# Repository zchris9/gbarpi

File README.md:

# gbarpi

# ibom
https://github.com/oceanofthelost/InteractivePCB

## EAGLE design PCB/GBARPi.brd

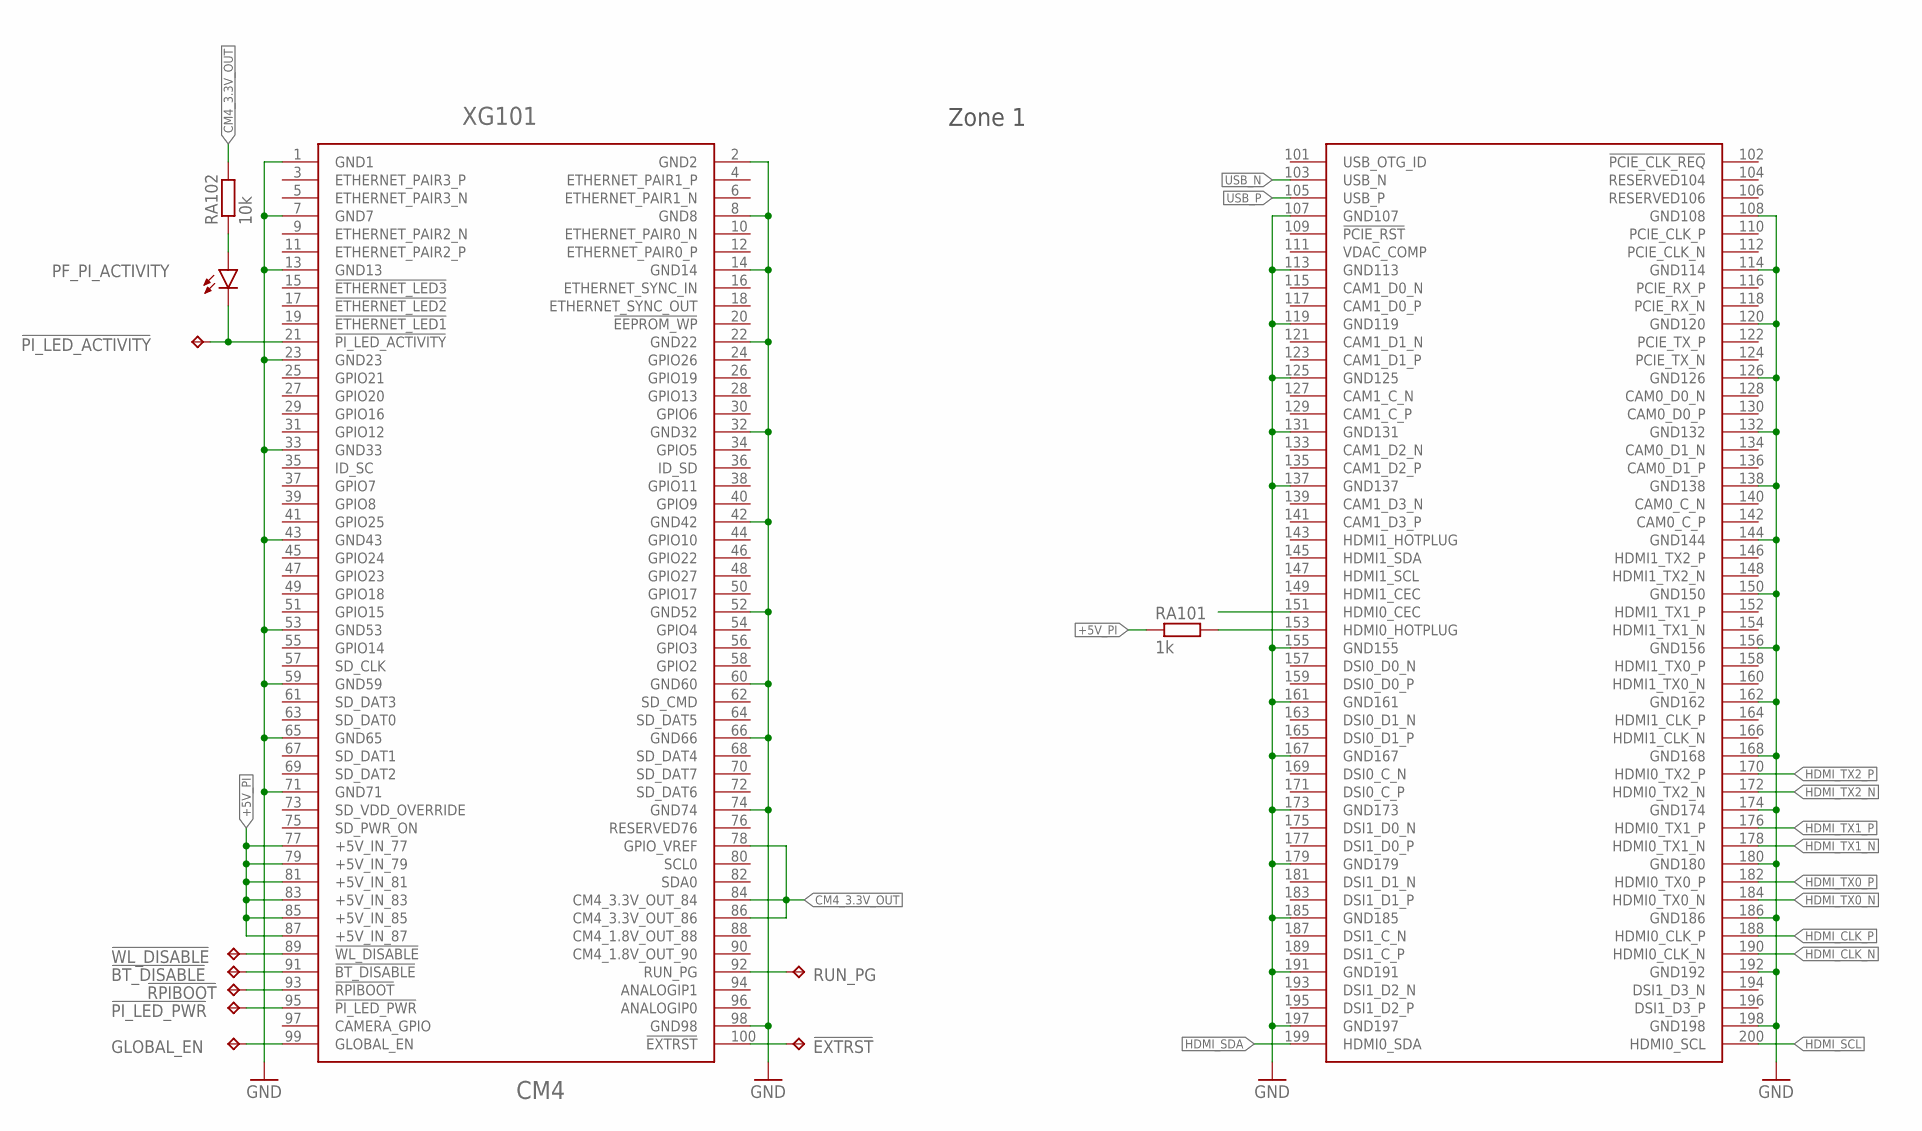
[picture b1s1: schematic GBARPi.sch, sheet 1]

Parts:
!BT_DISABLE: TPB1,27; B1,27
!EXTRST: TPB1,27; B1,27
!PI_LED_ACTIVITY: TPB1,27; B1,27
!PI_LED_PWR: TPB1,27; B1,27
!RPIBOOT: TPB1,27; B1,27
!WL_DISABLE: TPB1,27; B1,27
GLOBAL_EN: TPB1,27; B1,27
PF_PI_ACTIVITY: LEDCHIP-LED0603; CHIP-LED0603
RA101: 1k; R0402
RA102: 10k; R0402
RUN_PG: TPB1,27; B1,27
XG101: CM4

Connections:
!BT_DISABLE: !BT_DISABLE.TP, XG101.91 (!BT_DISABLE)
!EXTRST: !EXTRST.TP, XG101.100 (!EXTRST)
!PI_LED_ACTIVITY: !PI_LED_ACTIVITY.TP, PF_PI_ACTIVITY.C, XG101.21 (!PI_LED_ACTIVITY)
!PI_LED_PWR: !PI_LED_PWR.TP, XG101.95 (!PI_LED_PWR)
!RPIBOOT: !RPIBOOT.TP, XG101.93 (!RPIBOOT)
!WL_DISABLE: !WL_DISABLE.TP, XG101.89 (!WL_DISABLE)
+5V_PI: RA101.1, XG101.77 (+5V_IN_77), XG101.79 (+5V_IN_79), XG101.81 (+5V_IN_81), XG101.83 (+5V_IN_83), XG101.85 (+5V_IN_85), XG101.87 (+5V_IN_87); also elsewhere on the board
CM4_3.3V_OUT: RA102.2, XG101.78 (GPIO_VREF), XG101.84 (CM4_3.3V_OUT_84), XG101.86 (CM4_3.3V_OUT_86)
GLOBAL_EN: GLOBAL_EN.TP, XG101.99 (GLOBAL_EN)
GND: XG101.1 (GND1), XG101.2 (GND2), XG101.7 (GND7), XG101.8 (GND8), XG101.13 (GND13), XG101.14 (GND14), XG101.22 (GND22), XG101.23 (GND23), XG101.32 (GND32), XG101.33 (GND33), XG101.42 (GND42), XG101.43 (GND43), XG101.52 (GND52), XG101.53 (GND53), XG101.59 (GND59), XG101.60 (GND60), XG101.65 (GND65), XG101.66 (GND66), XG101.71 (GND71), XG101.74 (GND74), XG101.98 (GND98), XG101.107 (GND107), XG101.108 (GND108), XG101.113 (GND113), XG101.114 (GND114), XG101.119 (GND119), XG101.120 (GND120), XG101.125 (GND125), XG101.126 (GND126), XG101.131 (GND131), XG101.132 (GND132), XG101.137 (GND137), XG101.138 (GND138), XG101.144 (GND144), XG101.150 (GND150), XG101.155 (GND155), XG101.156 (GND156), XG101.161 (GND161), XG101.162 (GND162), XG101.167 (GND167), XG101.168 (GND168), XG101.173 (GND173), XG101.174 (GND174), XG101.179 (GND179), XG101.180 (GND180), XG101.185 (GND185), XG101.186 (GND186), XG101.191 (GND191), XG101.192 (GND192), XG101.197 (GND197), XG101.198 (GND198); also elsewhere on the board
HDMI_CLK_N: XG101.190 (HDMI0_CLK_N); also elsewhere on the board
HDMI_CLK_P: XG101.188 (HDMI0_CLK_P); also elsewhere on the board
HDMI_SCL: XG101.200 (HDMI0_SCL); also elsewhere on the board
HDMI_SDA: XG101.199 (HDMI0_SDA); also elsewhere on the board
HDMI_TX0_N: XG101.184 (HDMI0_TX0_N); also elsewhere on the board
HDMI_TX0_P: XG101.182 (HDMI0_TX0_P); also elsewhere on the board
HDMI_TX1_N: XG101.178 (HDMI0_TX1_N); also elsewhere on the board
HDMI_TX1_P: XG101.176 (HDMI0_TX1_P); also elsewhere on the board
HDMI_TX2_N: XG101.172 (HDMI0_TX2_N); also elsewhere on the board
HDMI_TX2_P: XG101.170 (HDMI0_TX2_P); also elsewhere on the board
unnamed: RA101.2, XG101.153 (HDMI0_HOTPLUG)
unnamed: PF_PI_ACTIVITY.A, RA102.1
RUN_PG: RUN_PG.TP, XG101.92 (RUN_PG)
USB_N: XG101.103 (USB_N); also elsewhere on the board
USB_P: XG101.105 (USB_P); also elsewhere on the board

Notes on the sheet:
Zone 1

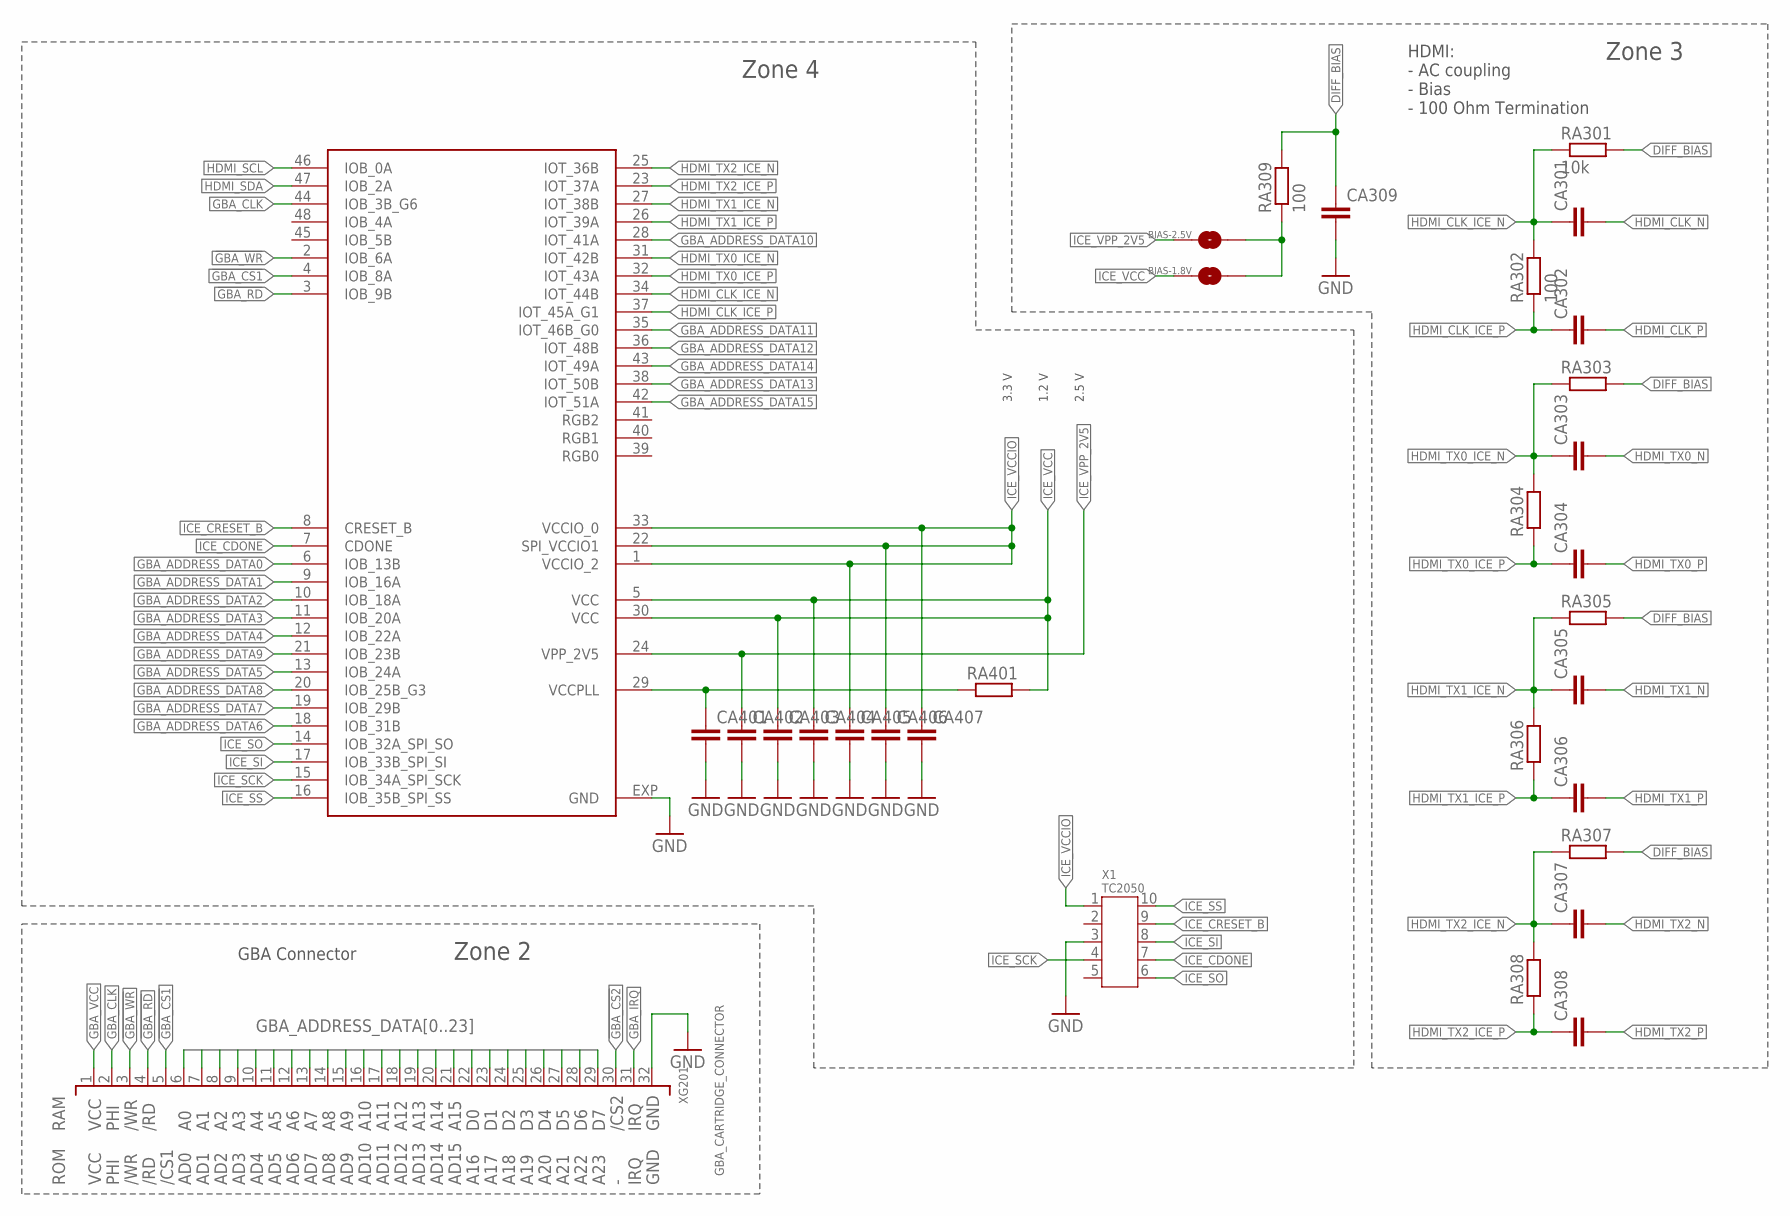
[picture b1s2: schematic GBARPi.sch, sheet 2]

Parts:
BIAS-1.8V: SJS-NC3
BIAS-2.5V: SJ
CA301, CA302, CA303, CA304, CA305, CA306, CA307, CA308, CA309, CA401, CA402, CA403, CA404, CA405, CA406, CA407: C-EUC0402; C0402
KF401: ICE40UP5KSG48; QFN50P700X700X100-49T535N
RA301: 10k; R0402
RA302, RA309: 100; R0402
RA303, RA304, RA305, RA306, RA307, RA308, RA401: R-EU_R0402; R0402
X1: TC2050
XG201: GBA_CARTRIDGE_CONNECTOR

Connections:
!GBA_CS1: KF401.4 (IOB_8A), XG201.5 (/RCS)
!GBA_CS2: XG201.30 (/RS); also elsewhere on the board
!GBA_RD: KF401.3 (IOB_9B), XG201.4 (/RD); also elsewhere on the board
!GBA_WR: KF401.2 (IOB_6A), XG201.3 (/WR); also elsewhere on the board
DIFF_BIAS: CA309.1, RA301.2, RA303.2, RA305.2, RA307.2, RA309.2
GBA_ADDRESS_DATA0: KF401.6 (IOB_13B), XG201.6 (A0); also elsewhere on the board
GBA_ADDRESS_DATA1: KF401.9 (IOB_16A), XG201.7 (A1); also elsewhere on the board
GBA_ADDRESS_DATA2: KF401.10 (IOB_18A), XG201.8 (A2); also elsewhere on the board
GBA_ADDRESS_DATA3: KF401.11 (IOB_20A), XG201.9 (A3); also elsewhere on the board
GBA_ADDRESS_DATA4: KF401.12 (IOB_22A), XG201.10 (A4); also elsewhere on the board
GBA_ADDRESS_DATA5: KF401.13 (IOB_24A), XG201.11 (A5); also elsewhere on the board
GBA_ADDRESS_DATA6: KF401.18 (IOB_31B), XG201.12 (A6); also elsewhere on the board
GBA_ADDRESS_DATA7: KF401.19 (IOB_29B), XG201.13 (A7)
GBA_ADDRESS_DATA8: KF401.20 (IOB_25B_G3), XG201.14 (A8)
GBA_ADDRESS_DATA9: KF401.21 (IOB_23B), XG201.15 (A9)
GBA_ADDRESS_DATA10: KF401.28 (IOT_41A), XG201.16 (A10)
GBA_ADDRESS_DATA11: KF401.35 (IOT_46B_G0), XG201.17 (A11)
GBA_ADDRESS_DATA12: KF401.36 (IOT_48B), XG201.18 (A12)
GBA_ADDRESS_DATA13: KF401.38 (IOT_50B), XG201.19 (A13)
GBA_ADDRESS_DATA14: KF401.43 (IOT_49A), XG201.20 (A14)
GBA_ADDRESS_DATA15: KF401.42 (IOT_51A), XG201.21 (A15)
GBA_ADDRESS_DATA16: XG201.22 (D0); also elsewhere on the board
GBA_ADDRESS_DATA17: XG201.23 (D1); also elsewhere on the board
GBA_ADDRESS_DATA18: XG201.24 (D2); also elsewhere on the board
GBA_ADDRESS_DATA19: XG201.25 (D3); also elsewhere on the board
GBA_ADDRESS_DATA20: XG201.26 (D4); also elsewhere on the board
GBA_ADDRESS_DATA21: XG201.27 (D5); also elsewhere on the board
GBA_ADDRESS_DATA22: XG201.28 (D6); also elsewhere on the board
GBA_ADDRESS_DATA23: XG201.29 (D7); also elsewhere on the board
GBA_CLK: KF401.44 (IOB_3B_G6), XG201.2 (NC); also elsewhere on the board
GBA_IRQ: XG201.31 (VIN); also elsewhere on the board
GBA_VCC: XG201.1 (VDD); also elsewhere on the board
GND: CA309.2, CA401.2, CA402.2, CA403.2, CA404.2, CA405.2, CA406.2, CA407.2, KF401.EXP (GND), X1.3, XG201.32 (GND); also elsewhere on the board
HDMI_CLK_ICE_N: CA301.1, KF401.34 (IOT_44B), RA301.1, RA302.2
HDMI_CLK_ICE_P: CA302.1, KF401.37 (IOT_45A_G1), RA302.1
HDMI_CLK_N: CA301.2; also elsewhere on the board
HDMI_CLK_P: CA302.2; also elsewhere on the board
HDMI_SCL: KF401.46 (IOB_0A); also elsewhere on the board
HDMI_SDA: KF401.47 (IOB_2A); also elsewhere on the board
HDMI_TX0_ICE_N: CA303.1, KF401.31 (IOT_42B), RA303.1, RA304.2
HDMI_TX0_ICE_P: CA304.1, KF401.32 (IOT_43A), RA304.1
HDMI_TX0_N: CA303.2; also elsewhere on the board
HDMI_TX0_P: CA304.2; also elsewhere on the board
HDMI_TX1_ICE_N: CA305.1, KF401.27 (IOT_38B), RA305.1, RA306.2
HDMI_TX1_ICE_P: CA306.1, KF401.26 (IOT_39A), RA306.1
HDMI_TX1_N: CA305.2; also elsewhere on the board
HDMI_TX1_P: CA306.2; also elsewhere on the board
HDMI_TX2_ICE_N: CA307.1, KF401.25 (IOT_36B), RA307.1, RA308.2
HDMI_TX2_ICE_P: CA308.1, KF401.23 (IOT_37A), RA308.1
HDMI_TX2_N: CA307.2; also elsewhere on the board
HDMI_TX2_P: CA308.2; also elsewhere on the board
ICE_CDONE: KF401.7 (CDONE), X1.7
ICE_CRESET_B: KF401.8 (CRESET_B), X1.9
ICE_SCK: KF401.15 (IOB_34A_SPI_SCK), X1.4
ICE_SI: KF401.17 (IOB_33B_SPI_SI), X1.8
ICE_SO: KF401.14 (IOB_32A_SPI_SO), X1.6
ICE_SS: KF401.16 (IOB_35B_SPI_SS), X1.10
ICE_VCC: BIAS-1.8V.1, CA403.1, CA404.1, KF401.5 (VCC), KF401.30 (VCC), RA401.2; also elsewhere on the board
ICE_VCCIO: CA405.1, CA406.1, CA407.1, KF401.1 (VCCIO_2), KF401.22 (SPI_VCCIO1), KF401.33 (VCCIO_0), X1.1; also elsewhere on the board
ICE_VPP_2V5: BIAS-2.5V.1, CA402.1, KF401.24 (VPP_2V5); also elsewhere on the board
unnamed: BIAS-1.8V.2, BIAS-2.5V.2, RA309.1
VCCPLL: CA401.1, KF401.29 (VCCPLL), RA401.1

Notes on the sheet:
HDMI: - AC coupling - Bias - 100 Ohm Termination
GBA Connector
3.3 V
1.2 V
2.5 V
Zone 2
Zone 3
Zone 4

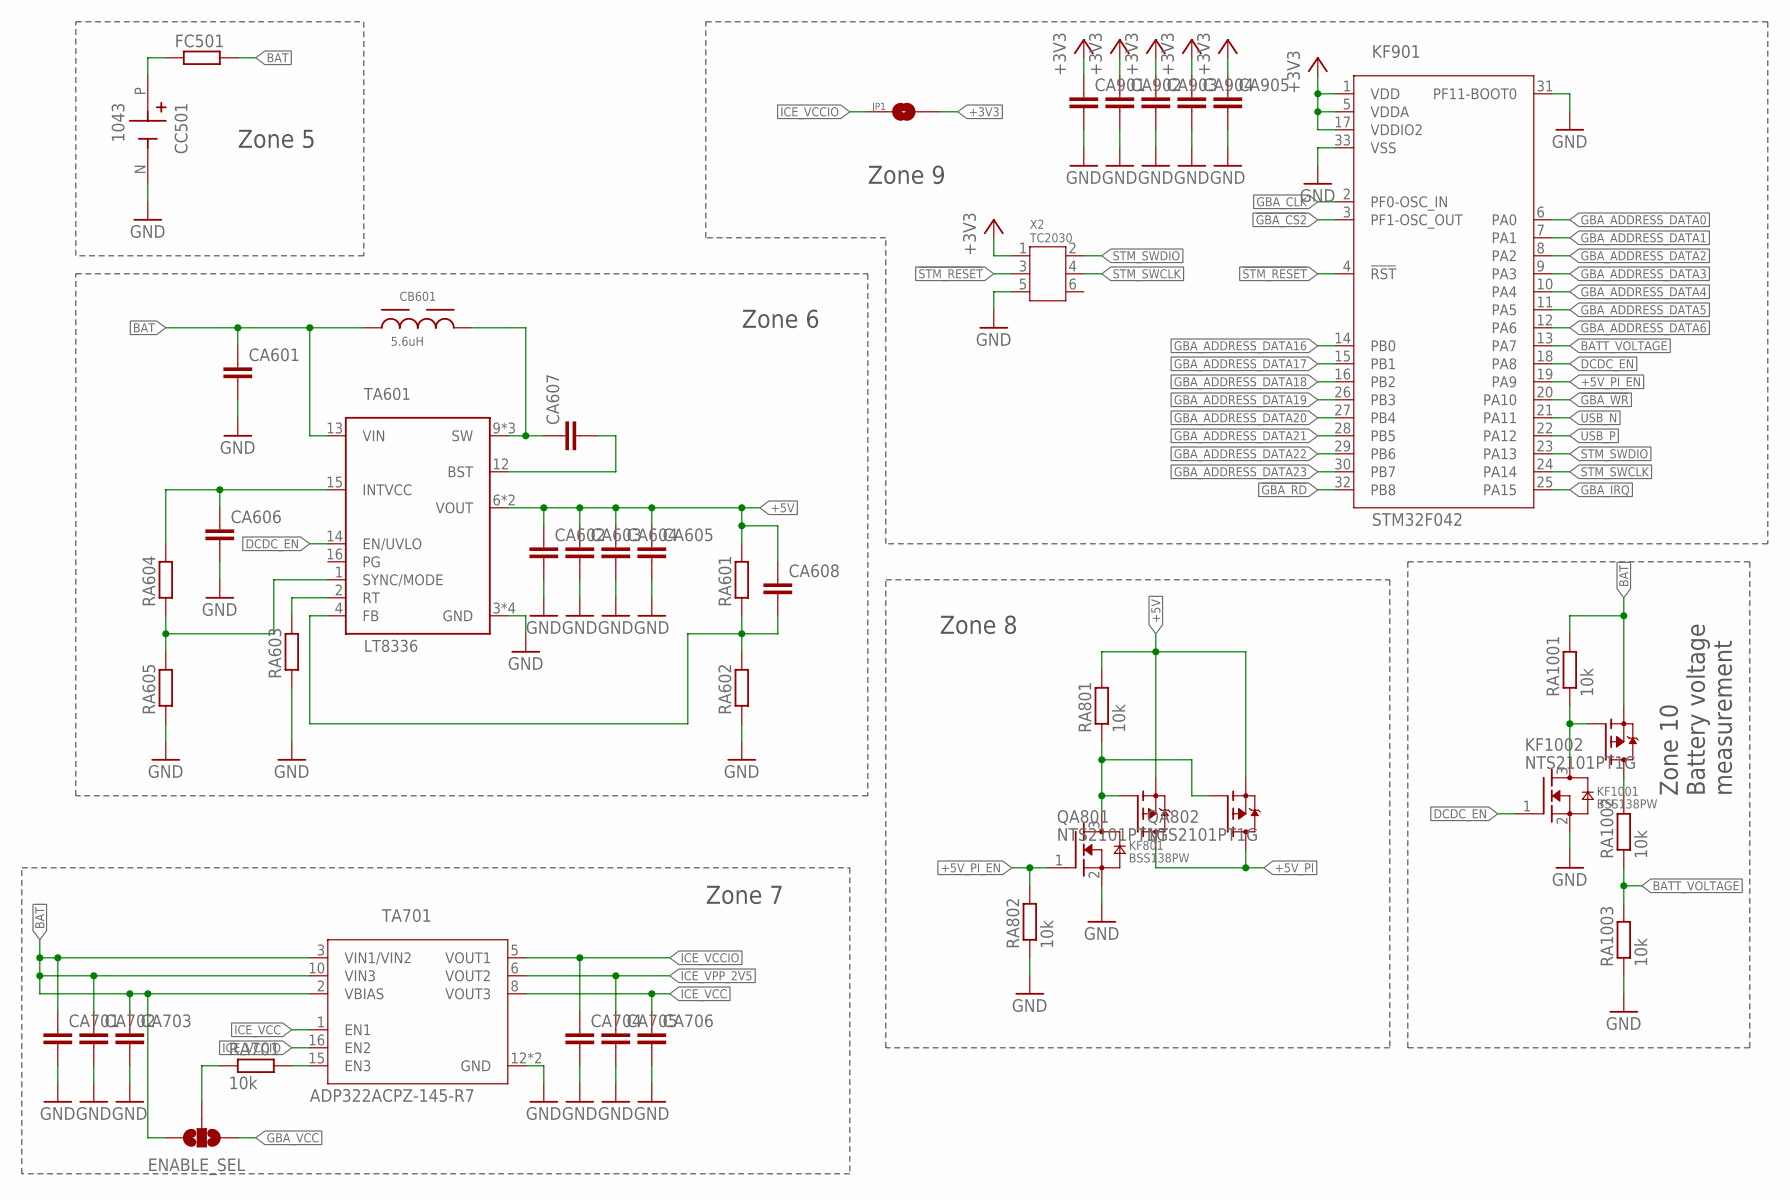
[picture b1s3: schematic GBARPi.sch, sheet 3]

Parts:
CA601, CA604, CA605: C-EUC1206; C1206
CA602, CA603: C-EUC0603; C0603
CA606, CA607, CA608, CA701, CA702, CA703, CA704, CA705, CA706, CA901, CA902, CA903, CA904, CA905: C-EUC0402; C0402
CB601: 5.6uH; WE-MAPI_4020
CC501: 1043; BAT_1043
ENABLE_SEL: SJ2W; SJ_2
FC501: R-EU_R1206; R1206
JP1: SJS-NC3
KF801, KF1001: BSS138PW; SC70-3
KF901: STM32F042; QFN50P500X500X60-33T350N
KF1002: NTS2101PT1G; SC70-3
QA801, QA802: NTS2101PT1G; SC70-3
RA601, RA602, RA603, RA604, RA605: R-EU_R0402; R0402
RA701, RA801, RA802, RA1001, RA1002, RA1003: 10k; R0402
TA601: LT8336; LQFN16
TA701: ADP322ACPZ-145-R7; QFN50P300X300X80-17T175N
X2: TC2030

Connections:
!GBA_CS2: KF901.3 (PF1-OSC_OUT); also elsewhere on the board
!GBA_RD: KF901.32 (PB8); also elsewhere on the board
!GBA_WR: KF901.20 (PA10); also elsewhere on the board
!STM_RESET: KF901.4 (!RST), X2.3
+3V3: CA901.1, CA902.1, CA903.1, CA904.1, CA905.1, JP1.2, KF901.1 (VDD), KF901.5 (VDDA), KF901.17 (VDDIO2), X2.1
+5V: CA602.1, CA603.1, CA604.1, CA605.1, CA608.1, QA801.2 (S), QA802.2 (S), RA601.2, RA801.2, TA601.6 (VOUT), TA601.7 (VOUT)
+5V_PI: QA801.3 (D), QA802.3 (D); also elsewhere on the board
+5V_PI_EN: KF801.1 (G), KF901.19 (PA9), RA802.2
BAT: CA601.1, CA701.1, CA702.1, CA703.1, CB601.1, ENABLE_SEL.3, FC501.2, KF1002.2 (S), RA1001.2, TA601.13 (VIN), TA701.2 (VBIAS), TA701.3 (VIN1/VIN2), TA701.10 (VIN3)
BATT_VOLTAGE: KF901.13 (PA7), RA1002.1, RA1003.2
BAT_UNFUSED: CC501.P, FC501.1
DCDC_EN: KF901.18 (PA8), KF1001.1 (G), TA601.14 (EN/UVLO)
GBA_ADDRESS_DATA0: KF901.6 (PA0); also elsewhere on the board
GBA_ADDRESS_DATA1: KF901.7 (PA1); also elsewhere on the board
GBA_ADDRESS_DATA2: KF901.8 (PA2); also elsewhere on the board
GBA_ADDRESS_DATA3: KF901.9 (PA3); also elsewhere on the board
GBA_ADDRESS_DATA4: KF901.10 (PA4); also elsewhere on the board
GBA_ADDRESS_DATA5: KF901.11 (PA5); also elsewhere on the board
GBA_ADDRESS_DATA6: KF901.12 (PA6); also elsewhere on the board
GBA_ADDRESS_DATA16: KF901.14 (PB0); also elsewhere on the board
GBA_ADDRESS_DATA17: KF901.15 (PB1); also elsewhere on the board
GBA_ADDRESS_DATA18: KF901.16 (PB2); also elsewhere on the board
GBA_ADDRESS_DATA19: KF901.26 (PB3); also elsewhere on the board
GBA_ADDRESS_DATA20: KF901.27 (PB4); also elsewhere on the board
GBA_ADDRESS_DATA21: KF901.28 (PB5); also elsewhere on the board
GBA_ADDRESS_DATA22: KF901.29 (PB6); also elsewhere on the board
GBA_ADDRESS_DATA23: KF901.30 (PB7); also elsewhere on the board
GBA_CLK: KF901.2 (PF0-OSC_IN); also elsewhere on the board
GBA_IRQ: KF901.25 (PA15); also elsewhere on the board
GBA_VCC: ENABLE_SEL.1; also elsewhere on the board
GND: CA601.2, CA602.2, CA603.2, CA604.2, CA605.2, CA606.2, CA701.2, CA702.2, CA703.2, CA704.2, CA705.2, CA706.2, CA901.2, CA902.2, CA903.2, CA904.2, CA905.2, CC501.N, KF801.2 (S), KF901.31 (PF11-BOOT0), KF901.33 (VSS), KF1001.2 (S), RA602.1, RA603.1, RA605.1, RA802.1, RA1003.1, TA601.3 (GND), TA601.5 (GND), TA601.8 (GND), TA601.TH (GND), TA701.12 (GND), TA701.17 (GND), X2.5; also elsewhere on the board
ICE_VCC: CA706.1, TA701.1 (EN1), TA701.8 (VOUT3); also elsewhere on the board
ICE_VCCIO: CA704.1, JP1.1, TA701.5 (VOUT1), TA701.16 (EN2); also elsewhere on the board
ICE_VPP_2V5: CA705.1, TA701.6 (VOUT2); also elsewhere on the board
LT8336_BST: CA607.2, TA601.12 (BST)
unnamed: CA608.2, RA601.1, RA602.2, TA601.4 (FB)
unnamed: CA607.1, CB601.2, TA601.9 (SW), TA601.10 (SW), TA601.11 (SW)
unnamed: RA603.2, TA601.2 (RT)
unnamed: RA604.1, RA605.2, TA601.1 (SYNC/MODE)
unnamed: KF801.3 (D), QA801.1 (G), QA802.1 (G), RA801.1
unnamed: CA606.1, RA604.2, TA601.15 (INTVCC)
unnamed: RA701.2, TA701.15 (EN3)
unnamed: ENABLE_SEL.2, RA701.1
unnamed: KF1001.3 (D), KF1002.1 (G), RA1001.1
unnamed: KF1002.3 (D), RA1002.2
STM_SWCLK: KF901.24 (PA14), X2.4
STM_SWDIO: KF901.23 (PA13), X2.2
USB_N: KF901.21 (PA11); also elsewhere on the board
USB_P: KF901.22 (PA12); also elsewhere on the board

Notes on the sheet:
Zone 5
Zone 6
Zone 7
Zone 8
Zone 9
Zone 10 Battery voltage measurement

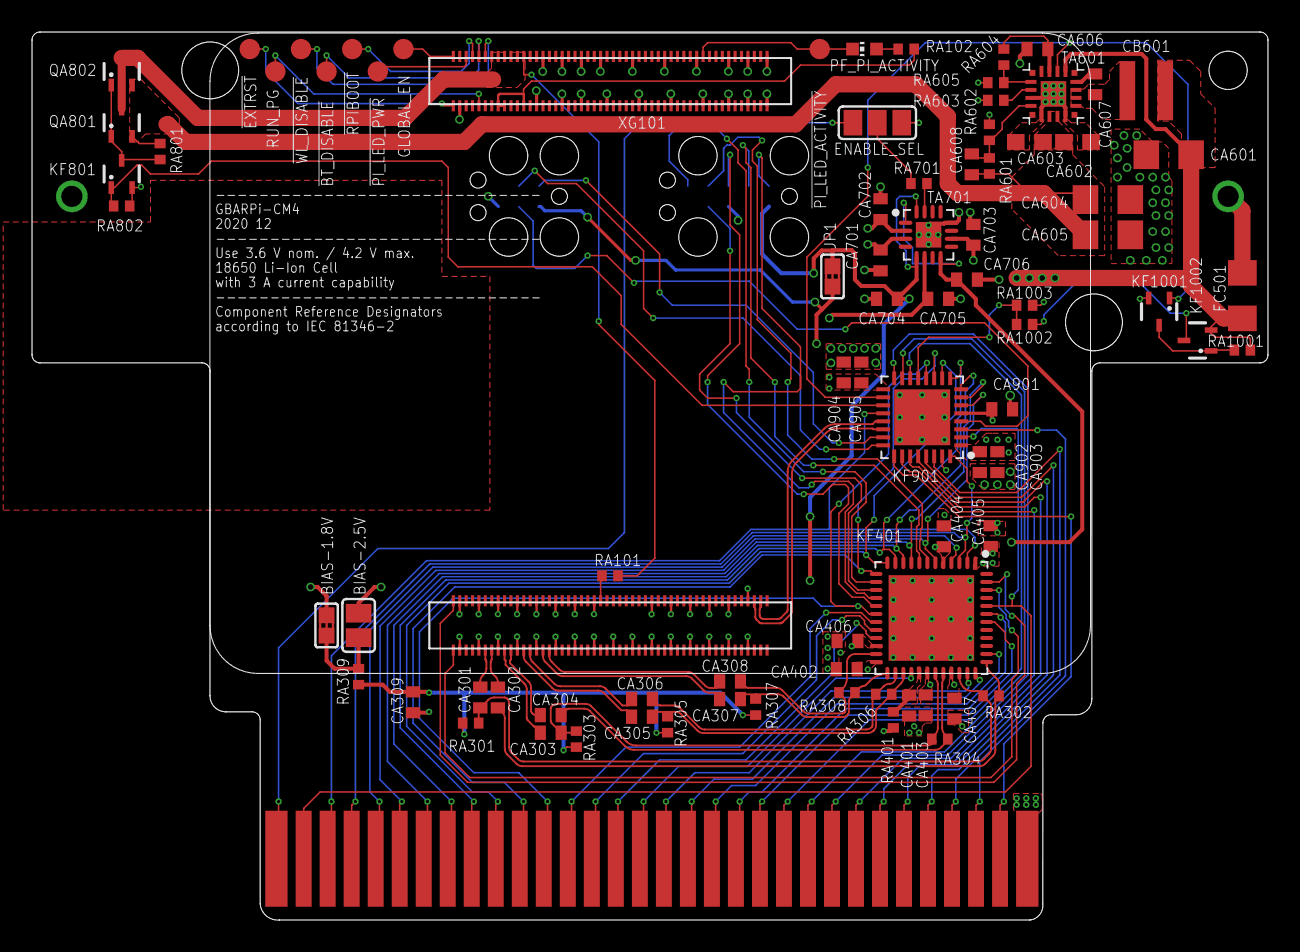
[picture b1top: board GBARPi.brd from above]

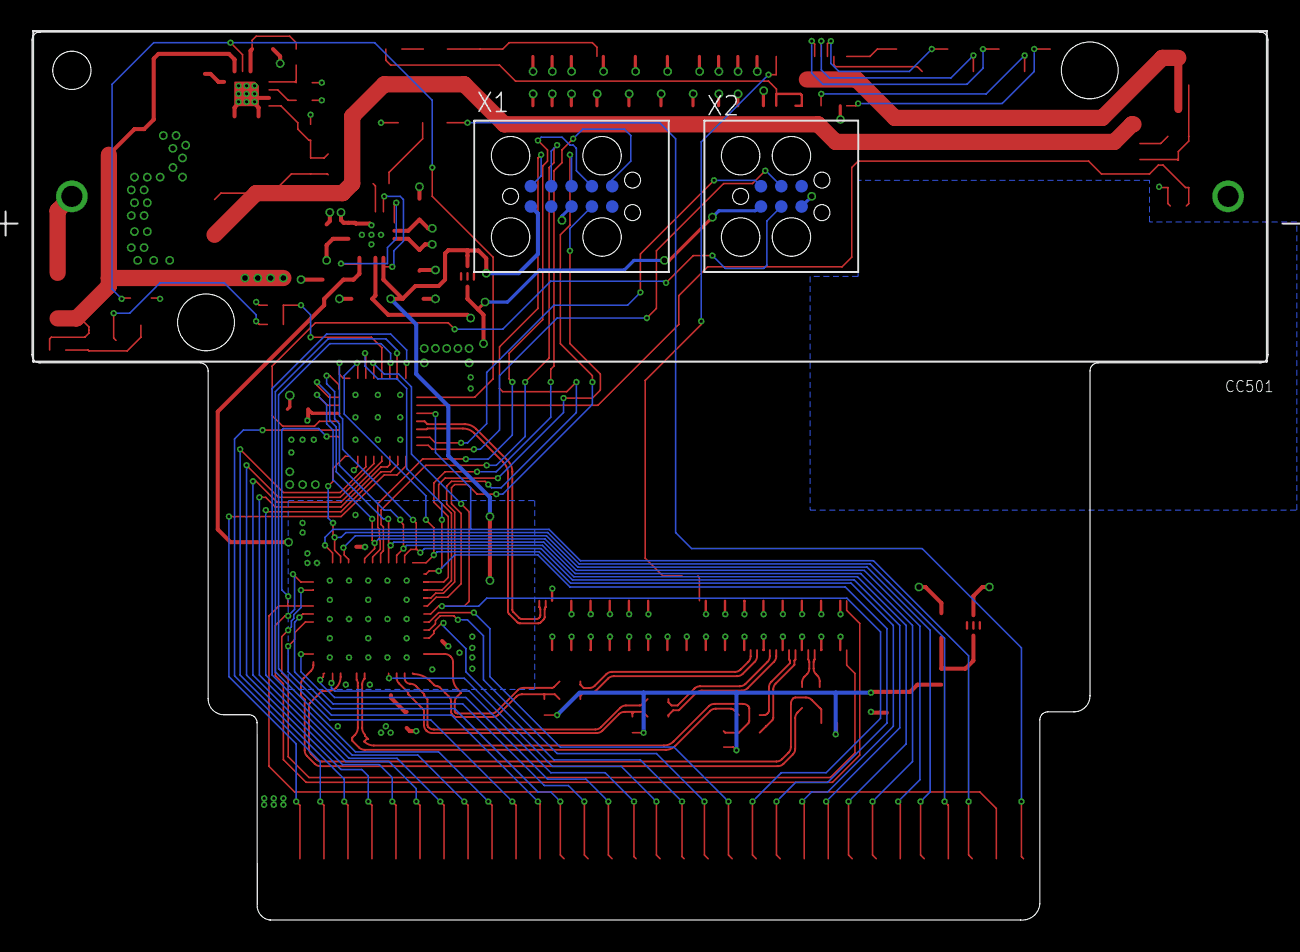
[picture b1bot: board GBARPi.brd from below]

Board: 4 copper layers, 77.2 x 55.5 mm, 87 parts (3 on the bottom side), 97 nets.

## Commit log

2020-12-06 New CM4 version - untested
2021-09-28 added ibom files

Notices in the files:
parts and their libraries:
Wurth_Power Magnetics_WE-MAPI: Copyright: Würth Elektronik
